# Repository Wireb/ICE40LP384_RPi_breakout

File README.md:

# ICE40LP384 to Raspberry Pi breakout
This repo is a collection of files related to my failed FPGA based quad scale interface board. 

The board worked but there was insufficient FPGA space for project. 

The FPGA board works and I was able to load simple projects from the Pi to the FPGA and communicate with it over SPI

## iCEcube2
The FPGA code was built with release 220.12.27943 using the free license key. See PiDRO vhdl for the source. Note this code is different than the version included in the python directory. I was not able to find the source to that version. 

## KiCad
This is a KiCad 6.x project. 

## Documentation

primary script is in the Python directory and called PiDRO.py. This loads the FPGA bitmap image to the card then communicates via the SPI bus. (The FPGA uses the SPI bus to load it's data then released the lines to internal IO control.) Note this tool uses "pigpiod" to control the Raspberry Pi's GPIOs and SPI interfaces. Make sure pigpiod is running before trying to use this script. 

There is a second script that uses GPIOzero and the SPI IO device. It worked but moved to pigpiod since it could do both SPI and GPIO in one tool. 

Either case the file you want after building the bitmap can be found in \iCEcube2\PiDRO_Implmnt\sbt\outputs\bitmap\PiDRO_bitmap.bin. The documentation was confusing and made it sound like a second tool was needed to generate the file. That is not the case just use iCEcube2 to generate the bitmap as part of the P&R steps then grab it from that directory. 

Copyright (c) 2022 Peter Shabino

Permission is hereby granted, free of charge, to any person obtaining a copy of this hardware, software, and associated documentation files 
(the "Product"), to deal in the Product without restriction, including without limitation the rights to use, copy, modify, merge, publish, 
distribute, sublicense, and/or sell copies of the Product, and to permit persons to whom the Product is furnished to do so, subject to the 
following conditions:

The above copyright notice and this permission notice shall be included in all copies or substantial portions of the Product.

THE PRODUCT IS PROVIDED "AS IS", WITHOUT WARRANTY OF ANY KIND, EXPRESS OR IMPLIED, INCLUDING BUT NOT LIMITED TO THE WARRANTIES OF 
MERCHANTABILITY, FITNESS FOR A PARTICULAR PURPOSE AND NONINFRINGEMENT. IN NO EVENT SHALL THE AUTHORS OR COPYRIGHT HOLDERS BE LIABLE 
FOR ANY CLAIM, DAMAGES OR OTHER LIABILITY, WHETHER IN AN ACTION OF CONTRACT, TORT OR OTHERWISE, ARISING FROM, OUT OF OR IN CONNECTION 
WITH THE PRODUCT OR THE USE OR OTHER DEALINGS IN THE PRODUCT.

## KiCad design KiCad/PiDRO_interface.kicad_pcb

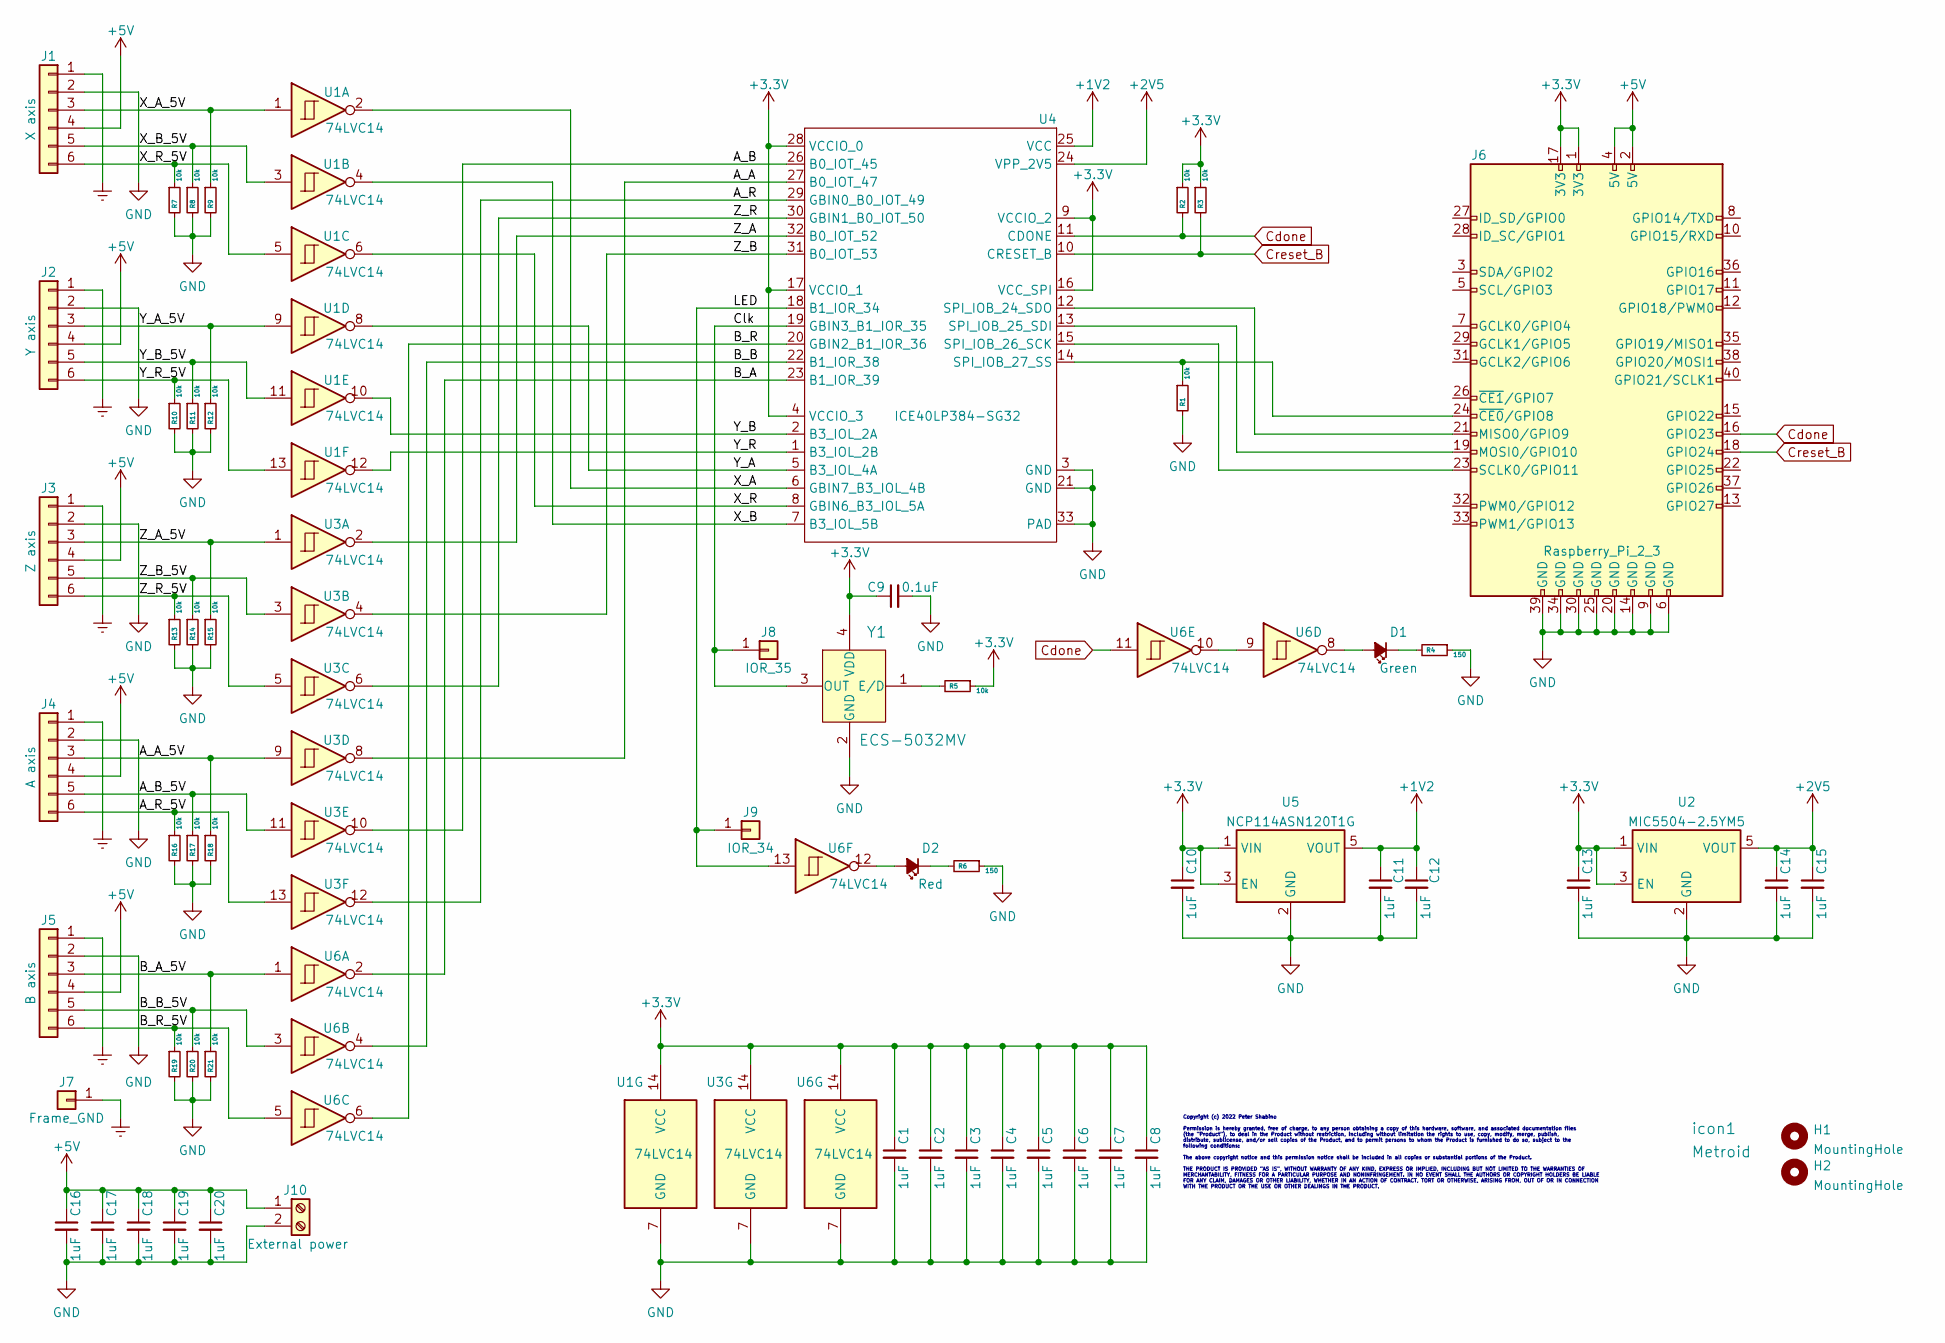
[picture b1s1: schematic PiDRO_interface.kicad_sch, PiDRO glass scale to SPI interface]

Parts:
C1, C2, C3, C4, C5, C6, C7, C8, C10, C11, C12, C13, C14, C15, C16, C17, C18, C19, C20: 1uF; C_0805_2012Metric
C9: 0.1uF; C_0603_1608Metric
D1: Green; LED_0805_2012Metric
D2: Red; LED_0805_2012Metric
H1, H2: MountingHole; MountingHole_2.7mm
J1: X axis; PinHeader_2x03_P2.54mm_Vertical
J2: Y axis; PinHeader_2x03_P2.54mm_Vertical
J3: Z axis; PinHeader_2x03_P2.54mm_Vertical
J4: A axis; PinHeader_2x03_P2.54mm_Vertical
J5: B axis; PinHeader_2x03_P2.54mm_Vertical
J6: Raspberry_Pi_2_3; Raspberry_Pi_Zero_Socketed_THT_FaceDown_MountingHoles
J7: Frame_GND; PinHeader_1x01_P2.54mm_Vertical
J8: IOR_35; PinHeader_1x01_P2.54mm_Vertical
J9: IOR_34; PinHeader_1x01_P2.54mm_Vertical
J10: External power; OSTTE020104
R1, R2, R3, R5, R7, R8, R9, R10, R11, R12, R13, R14, R15, R16, R17, R18, R19, R20, R21: 10k; R_0603_1608Metric
R4, R6: 150; R_0603_1608Metric
U1, U3, U6: 74LVC14; SO-14_5.3x10.2mm_P1.27mm
U2: MIC5504-2.5YM5; SOT-23-5
U4: ICE40LP384-SG32; TQFN-32-1EP_5x5mm_P0.5mm_EP2.1x2.1mm
U5: NCP114ASN120T1G; TSOP-5_1.65x3.05mm_P0.95mm
Y1: ECS-5032MV; Oscillator_XLH736022.579200I; MPN XLH736022.579200I; Digi-Key_PN 631-1277-ND
icon1: Metroid; metroid

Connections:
+1V2: C11.1, C12.1, U4.25 (VCC), U5.5 (VOUT)
+2V5: C14.1, C15.1, U2.5 (VOUT), U4.24 (VPP_2V5)
+3V3: C1.1, C2.1, C3.1, C4.1, C5.1, C6.1, C7.1, C8.1, C9.1, C10.1, C13.1, J6.1 (3V3), J6.17 (3V3), R2.1, R3.1, R5.1, U1.14 (VCC), U2.1 (VIN), U2.3 (EN), U3.14 (VCC), U4.4 (VCCIO_3), U4.9 (VCCIO_2), U4.16 (VCC_SPI), U4.17 (VCCIO_1), U4.28 (VCCIO_0), U5.1 (VIN), U5.3 (EN), U6.14 (VCC), Y1.4 (VDD)
+5V: C16.1, C17.1, C18.1, C19.1, C20.1, J1.4, J2.4, J3.4, J4.4, J5.4, J6.2 (5V), J6.4 (5V), J10.1
/A_A: U3.8, U4.27 (B0_IOT_47)
/A_B: U3.10, U4.26 (B0_IOT_45)
/A_R: U3.12, U4.29 (GBIN0_B0_IOT_49)
/B_A: U4.23 (B1_IOR_39), U6.2
/B_B: U4.22 (B1_IOR_38), U6.4
/B_R: U4.20 (GBIN2_B1_IOR_36), U6.6
/Clk: J8.1, U4.19 (GBIN3_B1_IOR_35), Y1.3 (OUT)
/LED: J9.1, U4.18 (B1_IOR_34), U6.13
/X_A: U1.2, U4.6 (GBIN7_B3_IOL_4B)
/X_B: U1.4, U4.7 (B3_IOL_5B)
/X_R: U1.6, U4.8 (GBIN6_B3_IOL_5A)
/Y_A: U1.8, U4.5 (B3_IOL_4A)
/Y_B: U1.10, U4.2 (B3_IOL_2A)
/Y_R: U1.12, U4.1 (B3_IOL_2B)
/Z_A: U3.2, U4.32 (B0_IOT_52)
/Z_B: U3.4, U4.31 (B0_IOT_53)
/Z_R: U3.6, U4.30 (GBIN1_B0_IOT_50)
Cdone: J6.16 (GPIO23), R2.2, U4.11 (CDONE), U6.11
Creset_B: J6.18 (GPIO24), R3.2, U4.10 (CRESET_B)
Earth: J1.1, J2.1, J3.1, J4.1, J5.1, J7.1
unnamed: D1.1 (K), R4.2
unnamed: D1.2 (A), U6.8
unnamed: D2.1 (K), R6.2
unnamed: D2.2 (A), U6.12
unnamed: J6.19 (MOSI0/GPIO10), U4.13 (SPI_IOB_25_SDI)
unnamed: J6.21 (MISO0/GPIO9), U4.12 (SPI_IOB_24_SDO)
unnamed: J6.23 (SCLK0/GPIO11), U4.15 (SPI_IOB_26_SCK)
unnamed: J6.24 (~CE0/GPIO8), R1.1, U4.14 (SPI_IOB_27_SS)
unnamed: R5.2, Y1.1 (E/D)
unnamed: U6.9, U6.10

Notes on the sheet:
Copyright (c) 2022 Peter Shabino Permission is hereby granted, free of charge, to any person obtaining a copy of this hardware, software, and associated documentation files (the "Product"), to deal in the Product without restriction, including without limitation the rights to use, copy, modify, mer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

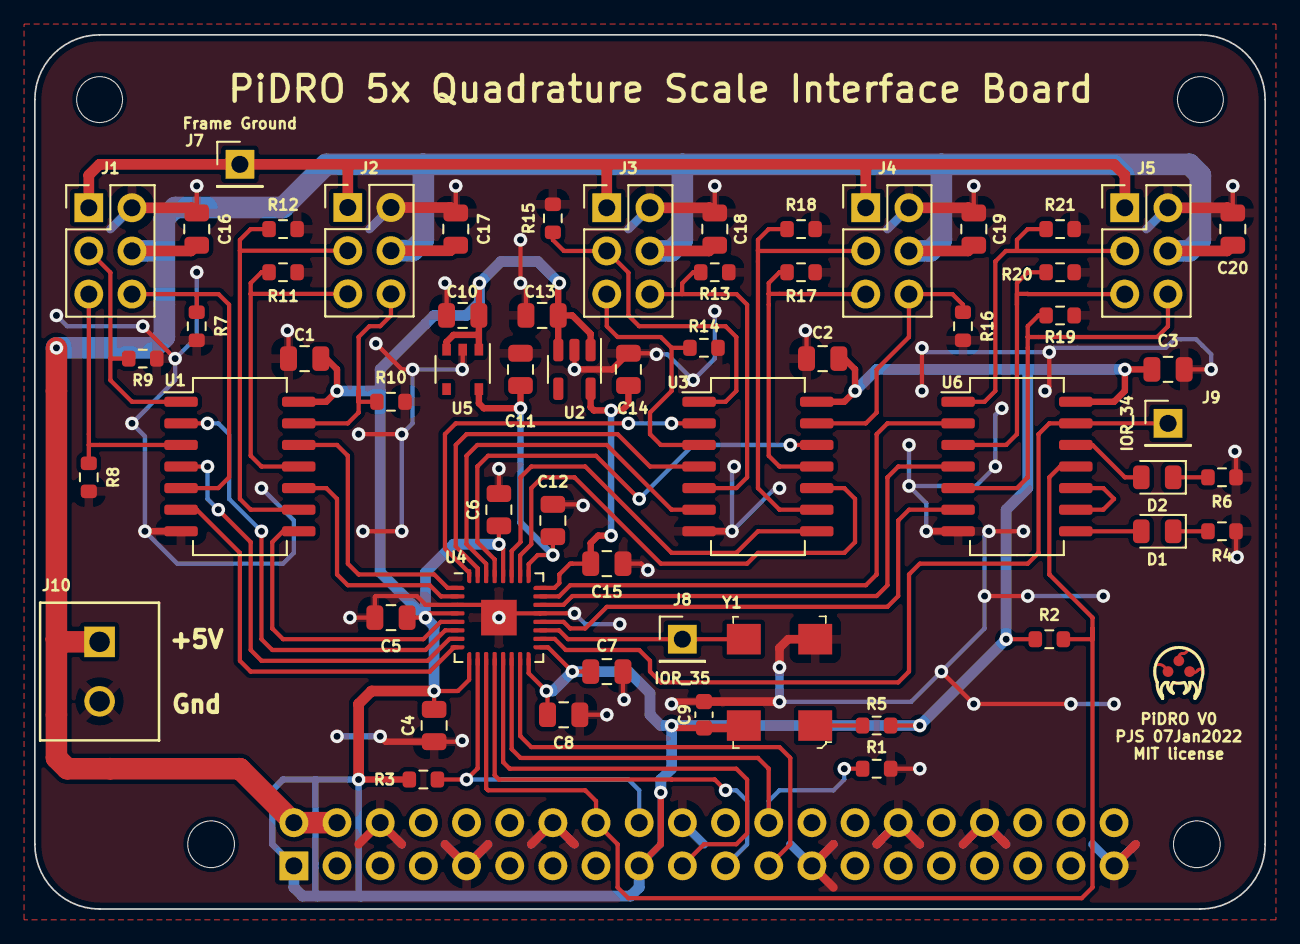
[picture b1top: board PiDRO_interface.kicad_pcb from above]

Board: 2 copper layers, 72.4 x 51.4 mm, 63 parts (1 on the bottom side), 50 nets.

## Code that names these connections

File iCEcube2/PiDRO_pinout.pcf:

set_io Y_R 1
set_io Y_B 2
set_io Y_A 5
set_io X_A 6
set_io X_B 7
set_io X_R 8
set_io SPI_SDO 12
set_io SPI_SDI 13
set_io SPI_SCK 15
set_io SPI_SS 14
set_io LED 18
set_io CLK 19
set_io B_R 20
set_io B_B 22
set_io B_A 23
set_io A_B 26
set_io A_A 27
set_io A_R 29
set_io Z_R 30
set_io Z_A 32
set_io Z_B 31

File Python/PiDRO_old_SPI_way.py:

# IO map
# GPIO8 - SPI SS - pull down
# GPIO9 - SPI MISO0
# GPIO10 - SPI MOSI0
# GPIO11 - SCLK0
# GPIO23 - Cdone - pull up - green LED when high
# GPIO24 - Creset_B - pull up 

# gpiozero documentation https://gpiozero.readthedocs.io/en/stable/recipes.html



import gpiozero
import time
import spidev
import sys

bitmap_file = "./test_bitmap.bin"

# open GPIO pins
Creset_B = gpiozero.OutputDevice("GPIO24", initial_value=None) # inital_value=None leaves the pin in previous state vs setting low by default. 
Cdone = gpiozero.InputDevice("GPIO23")  # pull_up = false, active_state = none (polarity inverse), pin_factory = none
SPI_SS = gpiozero.OutputDevice("GPIO8")




# create SPI object and open it. (note not using the correct CE pin intentional to give the config code manual control over it) 
spi = spidev.SpiDev()       # create spi object 
spi.open(0, 1)              # connecting to /dev/spidev0.0 (second digit is the CEx line to use) 
#spi.cshigh = True          # This no longer works due to a kernel change ;( have to manually control SS and burn a extra IO pin for the SPI controlled SS to be dumped on. 
spi.lsbfirst = False        # xmit LSB first
spi.max_speed_hz = 2000000  # set speed to 2MHz
spi.mode = 2                # cpol = 1 (clk idle high) CPHA = 0 (data sampled on rising edge)




#init FPGA
print("reset FPGA")
# drive Creset_B low to reset FPGA
Creset_B.off()
# drive SPI_SS low 
SPI_SS.off()
# hold reset for at least 200nS
time.sleep(1/1000000)  # 1uS

if(Cdone.is_active):
    print("Error occurred Cdone is active. Exiting")
    sys.exit(-1)

# release reset
Creset_B.on()
# allow at least 1200us for the iCE40 to clear internal memory
time.sleep(2000/1000000)  # 2000uS
print("Load FPGA image")
# drive SPI_SS high for 8 SPI clock cycles
SPI_SS.on()
spi.writebytes([0x00]) # this does a write. Note there is a max buffer size of 4069. 
# read in bitmap
print("  file "+bitmap_file)
file = open(bitmap_file, mode='rb')
bitmap_data = file.read()
file.close()
print("  Read "+str(len(bitmap_data))+" bitmap bytes")

if(Cdone.is_active):
    print("Cdone active")


# drive SS active (low)
SPI_SS.off()
# send full bitmap
spi.writebytes2(bitmap_data)  # note this function drops CE every 4096 bytes xmit (size of internal buffer) 
# drive SS inactive (high)
SPI_SS.on()

# send 100 more bytes
for x in range(100):
    spi.writebytes2([0x00])


#while(True):
#    SPI_SS.off()
 #   time.sleep(1)
  #  SPI_SS.on()
 #   print("Cdone = ",Cdone.is_active)
  #  if(Cdone.is_active):
   #     print("Cdone active")
    #time.sleep(1)
    


print("script done")
sys.exit()

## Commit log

2022-05-03 First push

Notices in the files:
KiCad/PiDRO_interface.kicad_pcb:
MIT license
